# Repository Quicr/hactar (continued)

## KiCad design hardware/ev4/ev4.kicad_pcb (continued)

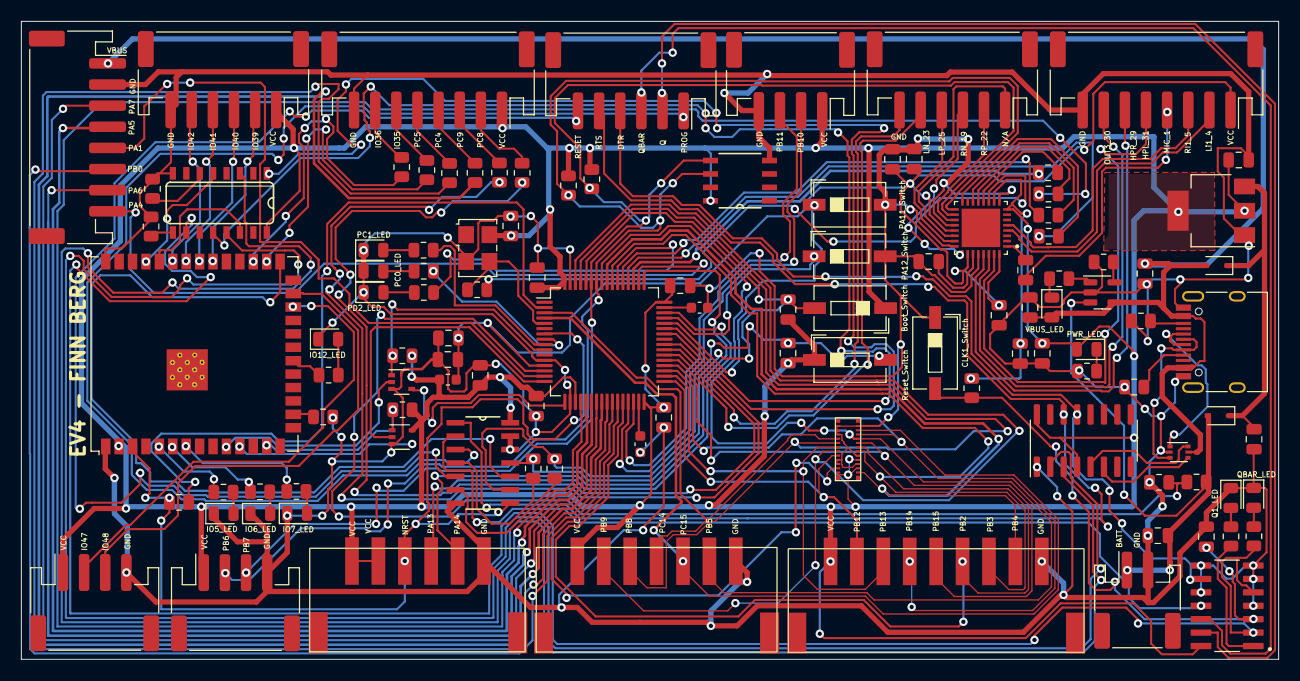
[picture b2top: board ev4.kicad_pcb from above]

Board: 2 copper layers, 119.0 x 60.4 mm, 111 parts (0 on the bottom side), 136 nets.

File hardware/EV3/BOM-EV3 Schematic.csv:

Comment,Designator,Footprint,LCSC
6.8k,R39,R_0805_2012Metric,C102042
NC7SZ125P5X,"U3,U9",SOT-353_SC-70-5,C12519
FerriteBead,120R1,L_0805_2012Metric,C127301
LED,"D1,D11,D3,D4,D5,D6,D7,D8,D9",LED_0805_2012Metric,C130114
DIODE,"D10,D2",D_0805_2012Metric,C133103
STM32F405RGTx,U1,LQFP-64_10x10mm_P0.5mm,C15742
USB_C_Receptacle,J9,USB_C_Receptacle_HRO_TYPE-C-31-M-12,C165948
10n,C8,C_0805_2012Metric,C1710
150,R1,R_0805_2012Metric,C17471
220,"R26,R30,R33,R34,R35",R_0805_2012Metric,C17557
4k7,"R13,R2,R3,R32,R4",R_0805_2012Metric,C17673
WM8960CGEFL/RV,U14,QFN50P500X500X90-33N,C18752
SG-5032CAN,X1,Oscillator_SMD_SeikoEpson_SG8002LB-4Pin_5.0x3.2mm,C1987261
100,"R14,R27,R28,R29,R31",R_0805_2012Metric,C212282
Conn_01x04_Female,"J3,J5,J7,J8",JST_PH_S4B-PH-SM4-TB_1x04-1MP_P2.00mm_Horizontal,C265102
Conn_01x08_Female,"J4,J6",JST_PH_S8B-PH-SM4-TB_1x08-1MP_P2.00mm_Horizontal,C265121
Conn_01x06_Female,J2,JST_PH_S6B-PH-SM4-TB_1x06-1MP_P2.00mm_Horizontal,C265405
SW_Push,"SW1,SW10,SW2,SW3,SW4,SW9",SW_DIP_SPSTx01_Slide_6.7x4.1mm_W6.73mm_P2.54mm_LowProfile_JPin,C266189
5k1,"R11,R12",R_0805_2012Metric,C27834
USBLC6-2P6,U4,SOT-666,C2827693
1u,"C10,C9",C_0805_2012Metric,C28323
1x6_connector,"U18,U5,U8",1x6_connector,C2845687
1x7_connector,U6,1x7_connector,C2845688
1x9_connector,U7,1x9_connector,C2845690
2k,R37,R_0805_2012Metric,C285226
560,"R10,R17,R18,R19,R20,R23,R24,R25,R9",R_0805_2012Metric,C28636
ESP32-S3-WROOM-1-N8R2,U11,ESP32-S3-WROOM-1-N8R2,C2913204
Conn_01x02_Female,J1,JST_PH_S2B-PH-SM4-TB_1x02-1MP_P2.00mm_Horizontal,C295747
AMS1117-3.3,U2,SOT-223-3_TabPin2,C351784
1k,R36,R_0805_2012Metric,C408924
4u7,"C1,C15,C19,C7",C_0805_2012Metric,C412634
MCP73832-2-OT,U12,SOT-23-5,C424093
BM20B(0.8)-24DS-0.4V(51),U16,BM20B(0.8)-24DS-0.4V(51),C424537
1k5,"R7,R8",R_0805_2012Metric,C4310
22u,C2,C_0805_2012Metric,C45783
10k,"R15,R16,R38",R_0805_2012Metric,C465472
100n,"C11,C12,C13,C14,C16,C17,C18,C20,C3,C4,C5,C6",C_0805_2012Metric,C49678
M24C02-RDW6TP,CR1,M24C02-RDW6TP,C83836
CH340C,U10,SOIC-16_3.9x9.9mm_P1.27mm,C84681

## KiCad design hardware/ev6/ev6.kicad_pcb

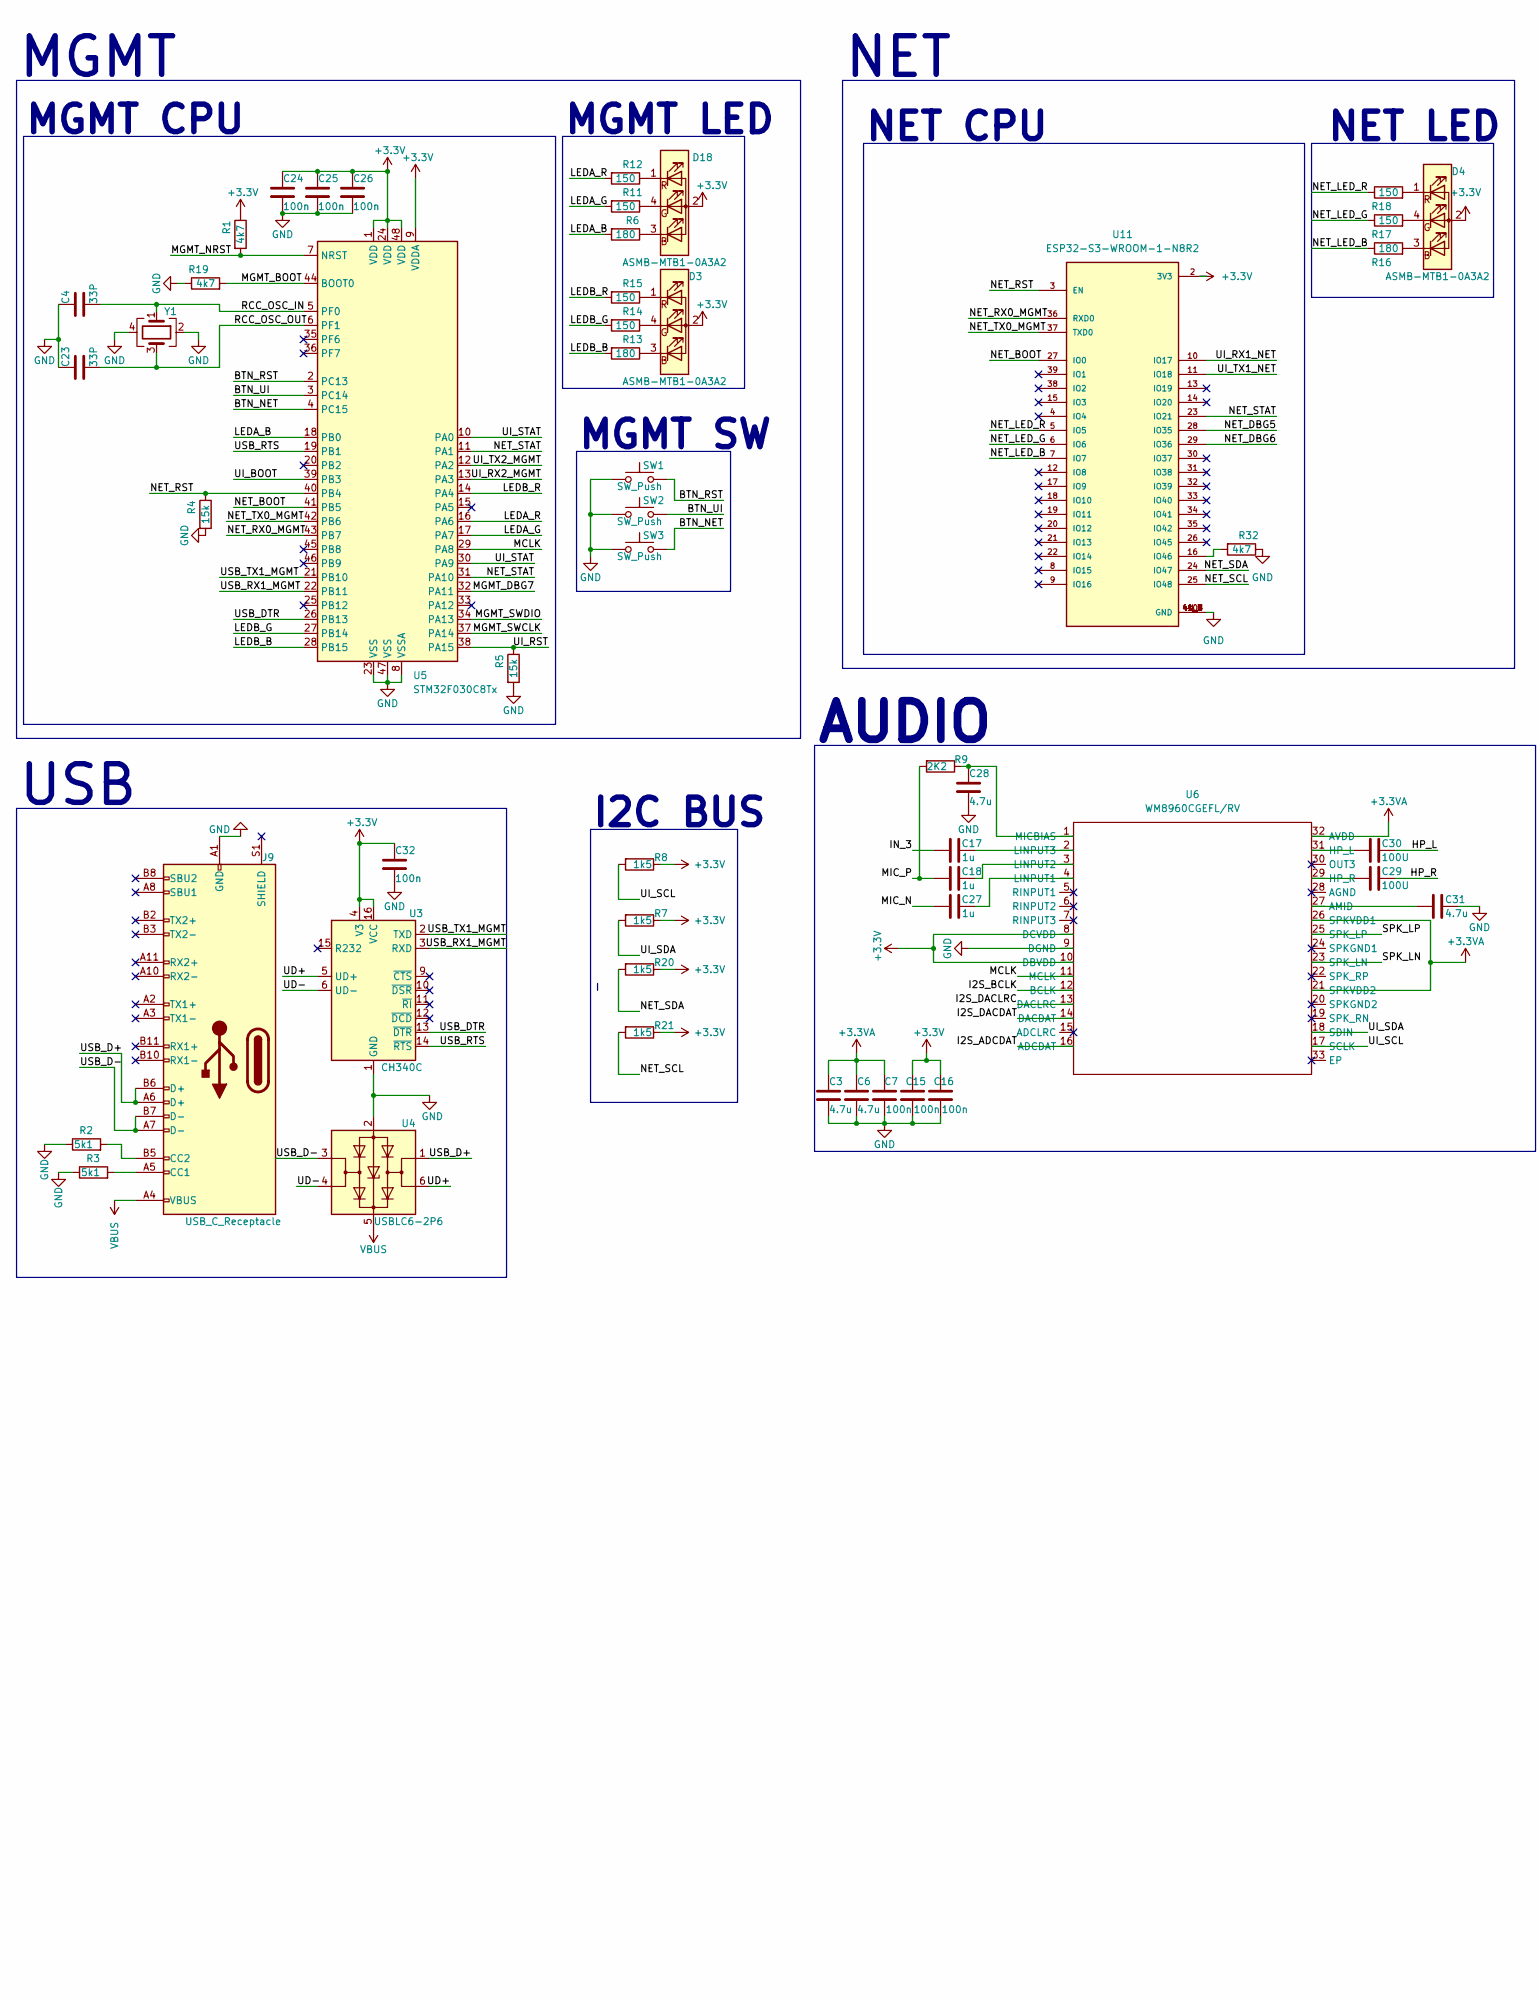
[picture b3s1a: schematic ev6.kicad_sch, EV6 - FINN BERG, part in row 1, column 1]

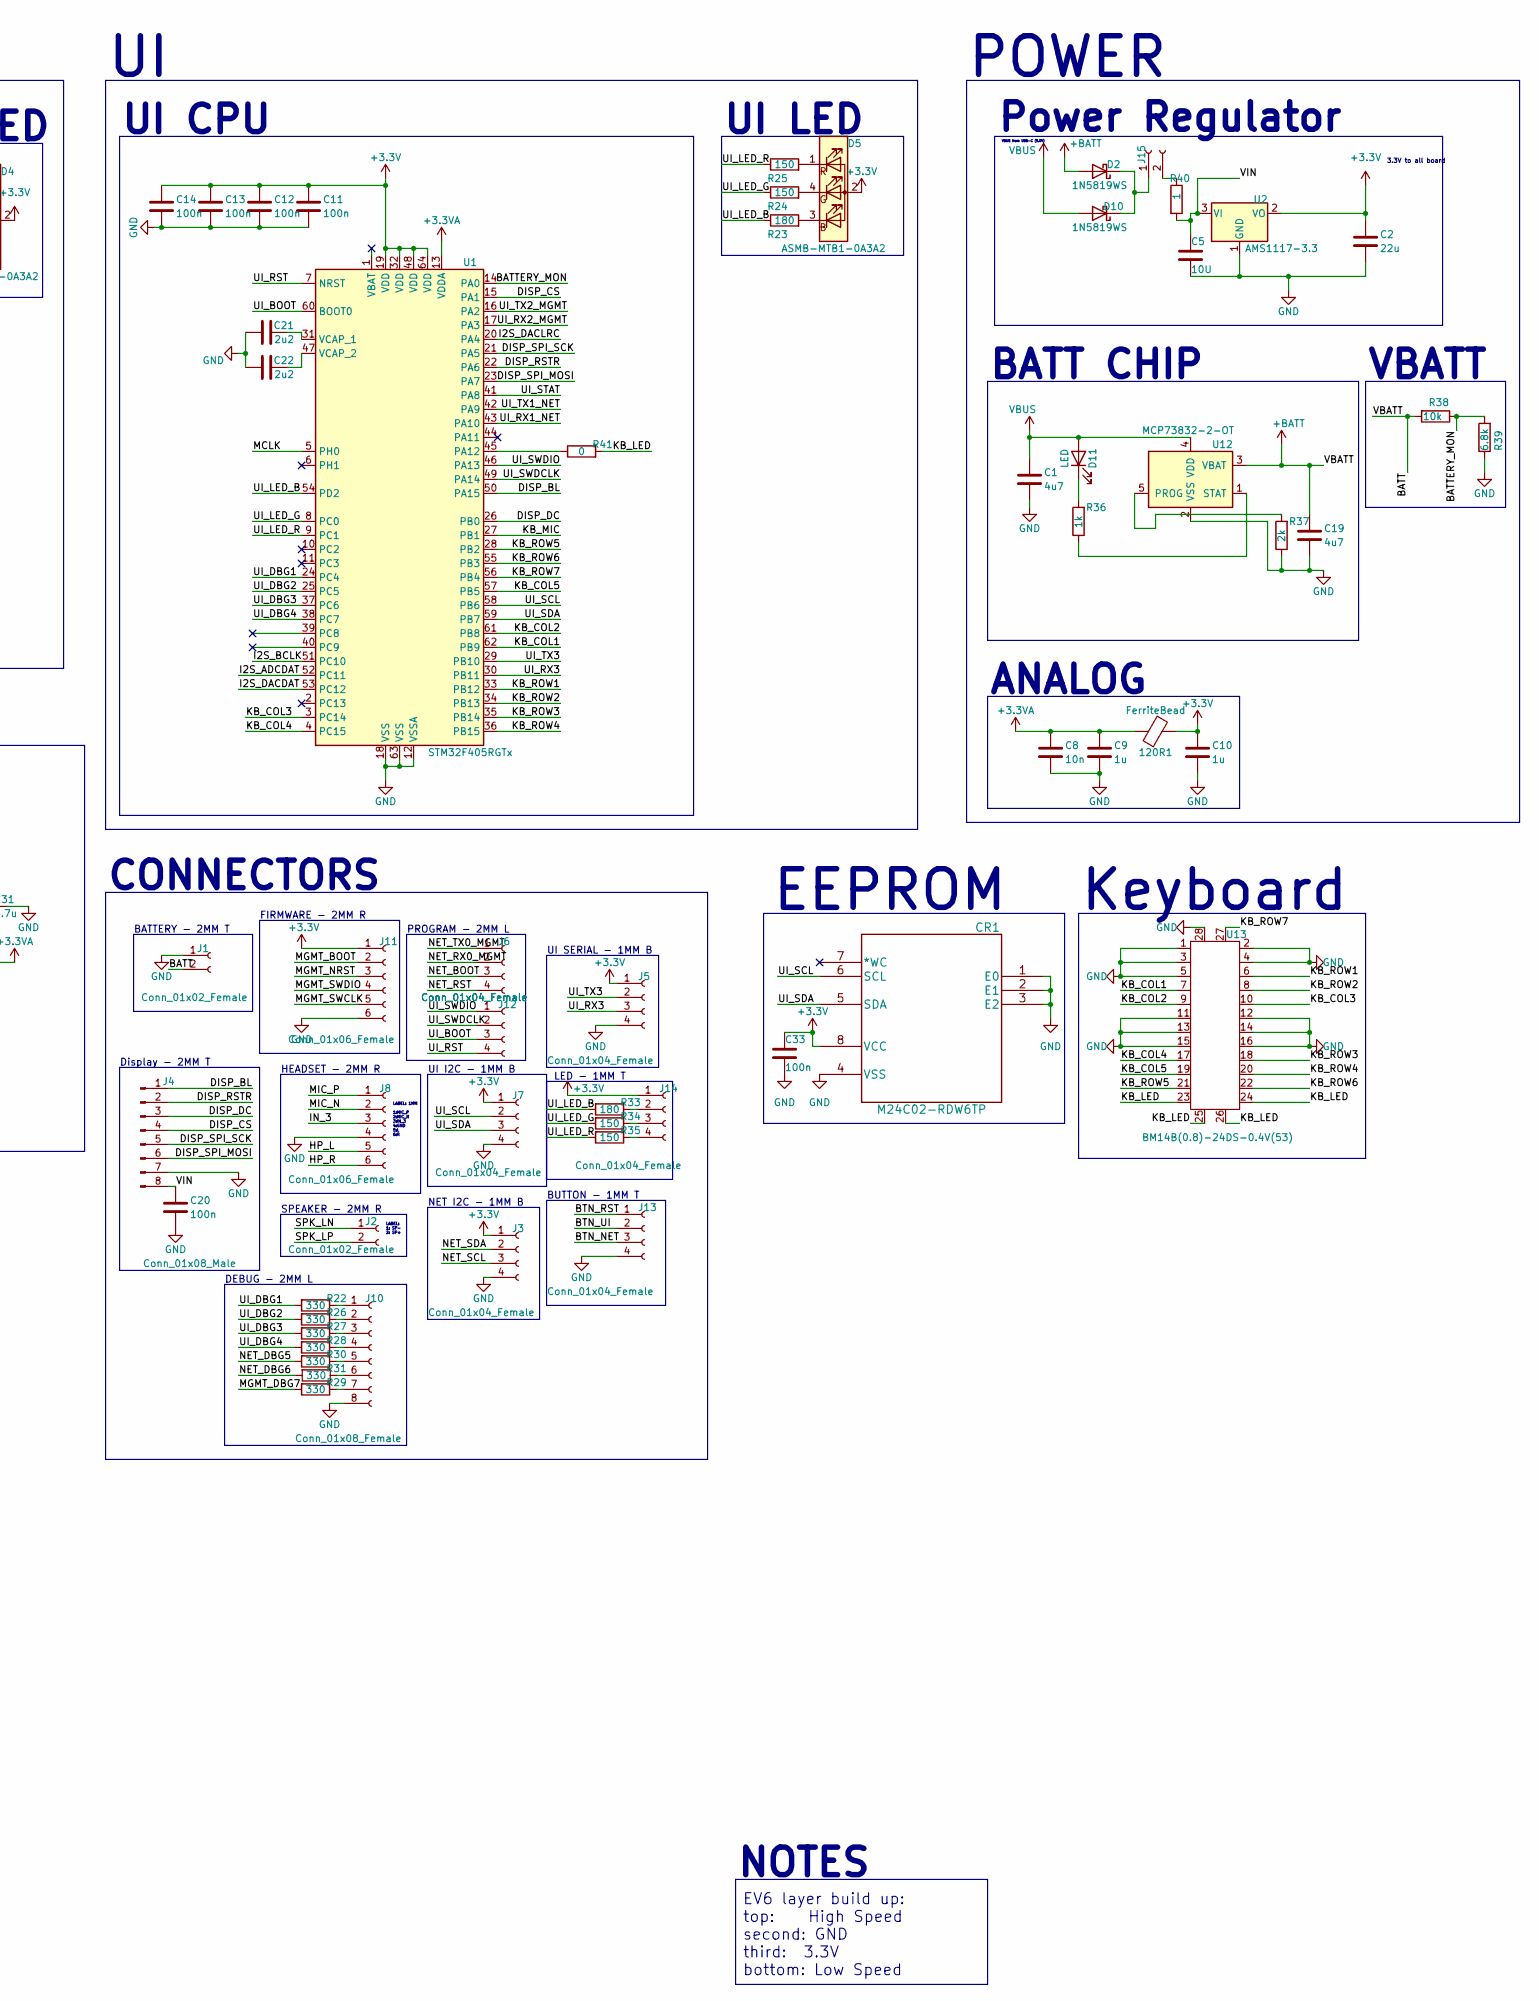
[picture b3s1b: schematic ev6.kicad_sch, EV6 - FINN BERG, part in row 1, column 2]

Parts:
120R1: FerriteBead; L_0603_1608Metric
C1, C19: 4u7; C_0402_1005Metric
C2: 22u; C_0402_1005Metric
C3, C6, C28, C31: 4.7u; C_0402_1005Metric
C4, C23: 33P; C_0805_2012Metric
C5: 10U; C_0402_1005Metric
C7, C11, C12, C13, C14, C15, C16, C20, C24, C25, C26, C32, C33: 100n; C_0402_1005Metric
C8: 10n; C_0402_1005Metric
C9, C10, C17, C18, C27: 1u; C_0402_1005Metric
C21, C22: 2u2; C_0402_1005Metric
C29, C30: 100U; C_1206_3216Metric
CR1: M24C02-RDW6TP; New_ESP32_M24C02-RMN6TP
D2, D10: 1N5819WS; D_SOD-323
D3, D4, D5, D18: ASMB-MTB1-0A3A2; LED RGB
D11: LED; LED_0805_2012Metric
J1, J2, J15: Conn_01x02_Female; JST_PH_S2B-PH-SM4-TB_1x02-1MP_P2.00mm_Horizontal
J3, J5, J6, J7, J12, J13, J14: Conn_01x04_Female; 1x4pin 1mm connector
J4: Conn_01x08_Male; PinHeader_1x08_P2.54mm_Vertical
J8, J11: Conn_01x06_Female; JST_PH_S6B-PH-SM4-TB_1x06-1MP_P2.00mm_Horizontal
J9: USB_C_Receptacle; USB_C_Receptacle_HRO_TYPE-C-31-M-12
J10: Conn_01x08_Female; JST_PH_S8B-PH-SM4-TB_1x08-1MP_P2.00mm_Horizontal
R1, R19, R32: 4k7; R_0402_1005Metric
R2, R3: 5k1; R_0402_1005Metric
R4, R5: 15k; R_0402_1005Metric
R6, R13, R16, R23, R33: 180; R_0402_1005Metric
R7, R8, R20, R21: 1k5; R_0402_1005Metric
R9: 2K2; R_0402_1005Metric
R11, R12, R14, R15, R17, R18, R24, R25, R34, R35: 150; R_0402_1005Metric
R22, R26, R27, R28, R29, R30, R31: 330; R_0402_1005Metric
R36: 1k; R_0402_1005Metric
R37: 2k; R_0402_1005Metric
R38: 10k; R_0402_1005Metric
R39: 6.8k; R_0402_1005Metric
R40: 1; R_0402_1005Metric
R41: 0; R_0402_1005Metric
SW1, SW2, SW3: SW_Push; SW_DIP_SPSTx01_Slide_6.7x4.1mm_W6.73mm_P2.54mm_LowProfile_J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
U1: STM32F405RGTx; LQFP-64_10x10mm_P0.5mm
U2: AMS1117-3.3; SOT-223-3_TabPin2
U3: CH340C; SOIC-16_3.9x9.9mm_P1.27mm
U4: USBLC6-2P6; SOT-666
U5: STM32F030C8Tx; LQFP-48_7x7mm_P0.5mm
U6: WM8960CGEFL/RV; QFN50P500X500X90-33N
U11: ESP32-S3-WROOM-1-N8R2; ESP32-S3-WROOM-1U
U12: MCP73832-2-OT; SOT-23-5
U13: BM14B(0.8)-24DS-0.4V(53); BM14B(0.B)-24DS-0.4V(53)
Y1: Crystal_GND24; Crystal_SMD_3225-4Pin_3.2x2.5mm

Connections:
+3.3V: 120R1.2, C2.1, C10.1, C11.1, C12.1, C13.1, C14.1, C15.2, C16.2, C24.1, C25.1, C26.1, C32.1, C33.1, CR1.8 (VCC), D3.2 (A), D4.2 (A), D5.2 (A), D18.2 (A), J3.1, J5.1, J7.1, J11.1, J14.1, R1.1, R7.1, R8.1, R20.1, R21.1, U1.19 (VDD), U1.32 (VDD), U1.48 (VDD), U1.64 (VDD), U2.2 (VO), U3.4 (V3), U3.16 (VCC), U5.1 (VDD), U5.9 (VDDA), U5.24 (VDD), U5.48 (VDD), U6.8 (DCVDD), U6.10 (DBVDD), U11.2 (3V3)
+3.3VA: 120R1.1, C3.1, C6.1, C7.2, C8.1, C9.1, U1.13 (VDDA), U6.21 (SPKVDD2), U6.26 (SPKVDD1), U6.32 (AVDD)
+BATT: C19.1, D2.2 (A), J1.2, R38.2, U12.3 (VBAT)
/BATTERY_MON: R38.1, R39.2, U1.14 (PA0)
/BTN_NET: J13.3, SW3.1, U5.4 (PC15)
/BTN_RST: J13.1, SW1.1, U5.2 (PC13)
/BTN_UI: J13.2, SW2.1, U5.3 (PC14)
/DISP_BL: J4.1, U1.50 (PA15)
/DISP_CS: J4.4, U1.15 (PA1)
/DISP_DC: J4.3, U1.26 (PB0)
/DISP_RSTR: J4.2, U1.22 (PA6)
/DISP_SPI_MOSI: J4.6, U1.23 (PA7)
/DISP_SPI_SCK: J4.5, U1.21 (PA5)
/HP_L: C30.2, J8.5
/HP_R: C29.2, J8.6
/I2S_ADCDAT: U1.52 (PC11), U6.16 (ADCDAT)
/I2S_BCLK: U1.51 (PC10), U6.12 (BCLK)
/I2S_DACDAT: U1.53 (PC12), U6.14 (DACDAT)
/I2S_DACLRC: U1.20 (PA4), U6.13 (DACLRC)
/IN_3: C17.1, J8.3
/KB_COL1: U1.62 (PB9), U13.7
/KB_COL2: U1.61 (PB8), U13.9
/KB_COL3: U1.3 (PC14), U13.10
/KB_COL4: U1.4 (PC15), U13.17
/KB_COL5: U1.57 (PB5), U13.19
/KB_LED: R41.2, U13.23, U13.24, U13.25, U13.26
/KB_MIC: U1.27 (PB1)
/KB_ROW1: U1.33 (PB12), U13.6
/KB_ROW2: U1.34 (PB13), U13.8
/KB_ROW3: U1.35 (PB14), U13.18
/KB_ROW4: U1.36 (PB15), U13.20
/KB_ROW5: U1.28 (PB2), U13.21
/KB_ROW6: U1.55 (PB3), U13.22
/KB_ROW7: U1.56 (PB4), U13.27
/LEDA_B: R6.2, U5.18 (PB0)
/LEDA_G: R11.2, U5.17 (PA7)
/LEDA_R: R12.2, U5.16 (PA6)
/LEDB_B: R13.2, U5.28 (PB15)
/LEDB_G: R14.2, U5.27 (PB14)
/LEDB_R: R15.2, U5.14 (PA4)
/MCLK: U1.5 (PH0), U5.29 (PA8), U6.11 (MCLK)
/MGMT_BOOT: J11.2, R19.2, U5.44 (BOOT0)
/MGMT_DBG7: R29.2, U5.32 (PA11)
/MGMT_NRST: J11.3, R1.2, U5.7 (NRST)
/MGMT_SWCLK: J11.5, U5.37 (PA14)
/MGMT_SWDIO: J11.4, U5.34 (PA13)
/MIC_N: C27.1, J8.2
/MIC_P: C18.1, J8.1, R9.2
/NET_BOOT: J6.3, U5.41 (PB5), U11.27 (IO0)
/NET_DBG5: R30.2, U11.28 (IO35)
/NET_DBG6: R31.2, U11.29 (IO36)
/NET_LED_B: R16.1, U11.7 (IO7)
/NET_LED_G: R17.1, U11.6 (IO6)
/NET_LED_R: R18.1, U11.5 (IO5)
/NET_RST: J6.4, R4.1, U5.40 (PB4), U11.3 (EN)
/NET_RX0_MGMT: J6.2, U5.43 (PB7), U11.36 (RXD0)
/NET_SCL: J3.3, R21.2, U11.25 (IO48)
/NET_SDA: J3.2, R20.2, U11.24 (IO47)
/NET_STAT: U5.11 (PA1), U5.31 (PA10), U11.23 (IO21)
/NET_TX0_MGMT: J6.1, U5.42 (PB6), U11.37 (TXD0)
/RCC_OSC_IN: C4.2, U5.5 (PF0), Y1.1
/RCC_OSC_OUT: C23.2, U5.6 (PF1), Y1.3
/SPK_LN: J2.1, U6.23 (SPK_LN)
/SPK_LP: J2.2, U6.25 (SPK_LP)
/UD+: U3.5 (UD+), U4.6 (I/O1)
/UD-: U3.6 (UD-), U4.4 (I/O2)
/UI_BOOT: J12.3, U1.60 (BOOT0), U5.39 (PB3)
/UI_DBG1: R22.2, U1.24 (PC4)
/UI_DBG2: R26.2, U1.25 (PC5)
/UI_DBG3: R27.2, U1.37 (PC6)
/UI_DBG4: R28.2, U1.38 (PC7)
/UI_LED_B: R23.1, R33.2, U1.54 (PD2)
/UI_LED_G: R24.1, R34.2, U1.8 (PC0)
/UI_LED_R: R25.1, R35.2, U1.9 (PC1)
/UI_RST: J12.4, R5.1, U1.7 (NRST), U5.38 (PA15)
/UI_RX1_NET: U1.43 (PA10), U11.10 (IO17)
/UI_RX2_MGMT: U1.17 (PA3), U5.13 (PA3)
/UI_RX3: J5.3, U1.30 (PB11)
/UI_SCL: CR1.6 (SCL), J7.2, R8.2, U1.58 (PB6), U6.17 (SCLK)
/UI_SDA: CR1.5 (SDA), J7.3, R7.2, U1.59 (PB7), U6.18 (SDIN)
/UI_STAT: U1.41 (PA8), U5.10 (PA0), U5.30 (PA9)
/UI_SWDCLK: J12.2, U1.49 (PA14)
/UI_SWDIO: J12.1, U1.46 (PA13)
/UI_TX1_NET: U1.42 (PA9), U11.11 (IO18)
/UI_TX2_MGMT: U1.16 (PA2), U5.12 (PA2)
/UI_TX3: J5.2, U1.29 (PB10)
/USB_D+: J9.A6 (D+), J9.B6 (D+), U4.1 (I/O1)
/USB_D-: J9.A7 (D-), J9.B7 (D-), U4.3 (I/O2)
/USB_DTR: U3.13 (~DTR), U5.26 (PB13)
/USB_RTS: U3.14 (~RTS), U5.19 (PB1)
/USB_RX1_MGMT: U3.3 (RXD), U5.22 (PB11)
/USB_TX1_MGMT: U3.2 (TXD), U5.21 (PB10)
/VIN: C5.1, C20.1, J4.8, R40.2, U2.3 (VI)
GND: C1.2, C2.2, C3.2, C4.1, C5.2, C6.2, C7.1, C8.2, C9.2, C10.2, C11.2, C12.2, C13.2, C14.2, C15.1, C16.1, C19.2, C20.2, C21.1, C22.1, C23.1, C24.2, C25.2, C26.2, C28.2, C31.1, C32.2, C33.2, CR1.1 (E0), CR1.2 (E1), CR1.3 (E2), CR1.4 (VSS), J1.1, J3.4, J4.7, J5.4, J7.4, J8.4, J9.A1 (GND), J9.A12 (GND), J9.B1 (GND), J9.B12 (GND), J10.8, J11.6, J13.4, R2.1, R3.1, R4.2, R5.2, R19.1, R32.1, R37.1, R39.1, SW1.2, SW2.2, SW3.2, U1.12 (VSSA), U1.18 (VSS), U1.63 (VSS), U2.1 (GND), U3.1 (GND), U4.2 (GND), U5.8 (VSSA), U5.23 (VSS), U5.47 (VSS), U6.9 (DGND), U11.1 (GND), U11.40 (GND), U11.41_1 (GND), U11.41_2 (GND), U11.41_3 (GND), U11.41_4 (GND), U11.41_5 (GND), U11.41_6 (GND), U11.41_7 (GND), U11.41_8 (GND), U11.41_9 (GND), U12.2 (VSS), U13.1, U13.2, U13.3, U13.4, U13.5, U13.11, U13.12, U13.13, U13.14, U13.15, U13.16, U13.28, Y1.2, Y1.4
unnamed: C17.2, U6.2 (LINPUT3)
unnamed: C18.2, U6.3 (LINPUT2)
unnamed: C21.2, U1.31 (VCAP_1)
unnamed: C22.2, U1.47 (VCAP_2)
unnamed: C27.2, U6.4 (LINPUT1)
unnamed: C28.1, R9.1, U6.1 (MICBIAS)
unnamed: C29.1, U6.29 (HP_R)
unnamed: C30.1, U6.31 (HP_L)
unnamed: C31.2, U6.27 (AMID)
unnamed: D3.1 (RK), R15.1
unnamed: D3.3 (BK), R13.1
unnamed: D3.4 (GK), R14.1
unnamed: D4.1 (RK), R18.2
unnamed: D4.3 (BK), R16.2
unnamed: D4.4 (GK), R17.2
unnamed: D5.1 (RK), R25.2
unnamed: D5.3 (BK), R23.2
unnamed: D5.4 (GK), R24.2
unnamed: D2.1 (K), D10.1 (K), J15.1
unnamed: D11.1 (K), R36.2
unnamed: D18.1 (RK), R12.1
unnamed: D18.3 (BK), R6.1
unnamed: D18.4 (GK), R11.1
unnamed: J9.A5 (CC1), R3.2
unnamed: J9.B5 (CC2), R2.2
unnamed: J10.1, R22.1
unnamed: J10.2, R26.1
unnamed: J10.3, R27.1
unnamed: J10.4, R28.1
unnamed: J10.5, R30.1
unnamed: J10.6, R31.1
unnamed: J10.7, R29.1
unnamed: J14.2, R33.1
unnamed: J14.3, R34.1
unnamed: J14.4, R35.1
unnamed: J15.2, R40.1
unnamed: R32.2, U11.16 (IO46)
unnamed: R36.1, U12.1 (STAT)
unnamed: R37.2, U12.5 (PROG)
unnamed: R41.1, U1.45 (PA12)
VBUS: C1.1, D10.2 (A), D11.2 (A), J9.A4 (VBUS), J9.A9 (VBUS), J9.B4 (VBUS), J9.B9 (VBUS), U4.5 (VBUS), U12.4 (VDD)

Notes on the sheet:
MGMT
VBATT
SPEAKER - 2MM R
NET CPU
MGMT CPU
BATT CHIP
NET
POWER
PROGRAM - 2MM L
CONNECTORS
3.3V to all board
NET LED
UI CPU
HEADSET - 2MM R
BATTERY - 2MM T
BUTTON - 1MM T
EV6 layer build up: top: High Speed second: GND third: 3.3V bottom: Low Speed
LABEL: 1MM 1:MIC_P 2:MIC_N 3:IN_3 4:GND 5:L 6:R
AUDIO
MGMT SW
UI SERIAL - 1MM B
EEPROM
UI I2C - 1MM B
I2C BUS
FIRMWARE - 2MM R
USB
VBUS from USB-C (5.0V)
MGMT LED
LABEL: 1: SP- 2: SP+
LED - 1MM T
NOTES
Power Regulator
Keyboard
Display - 2MM T
DEBUG - 2MM L
UI LED
NET I2C - 1MM B
ANALOG

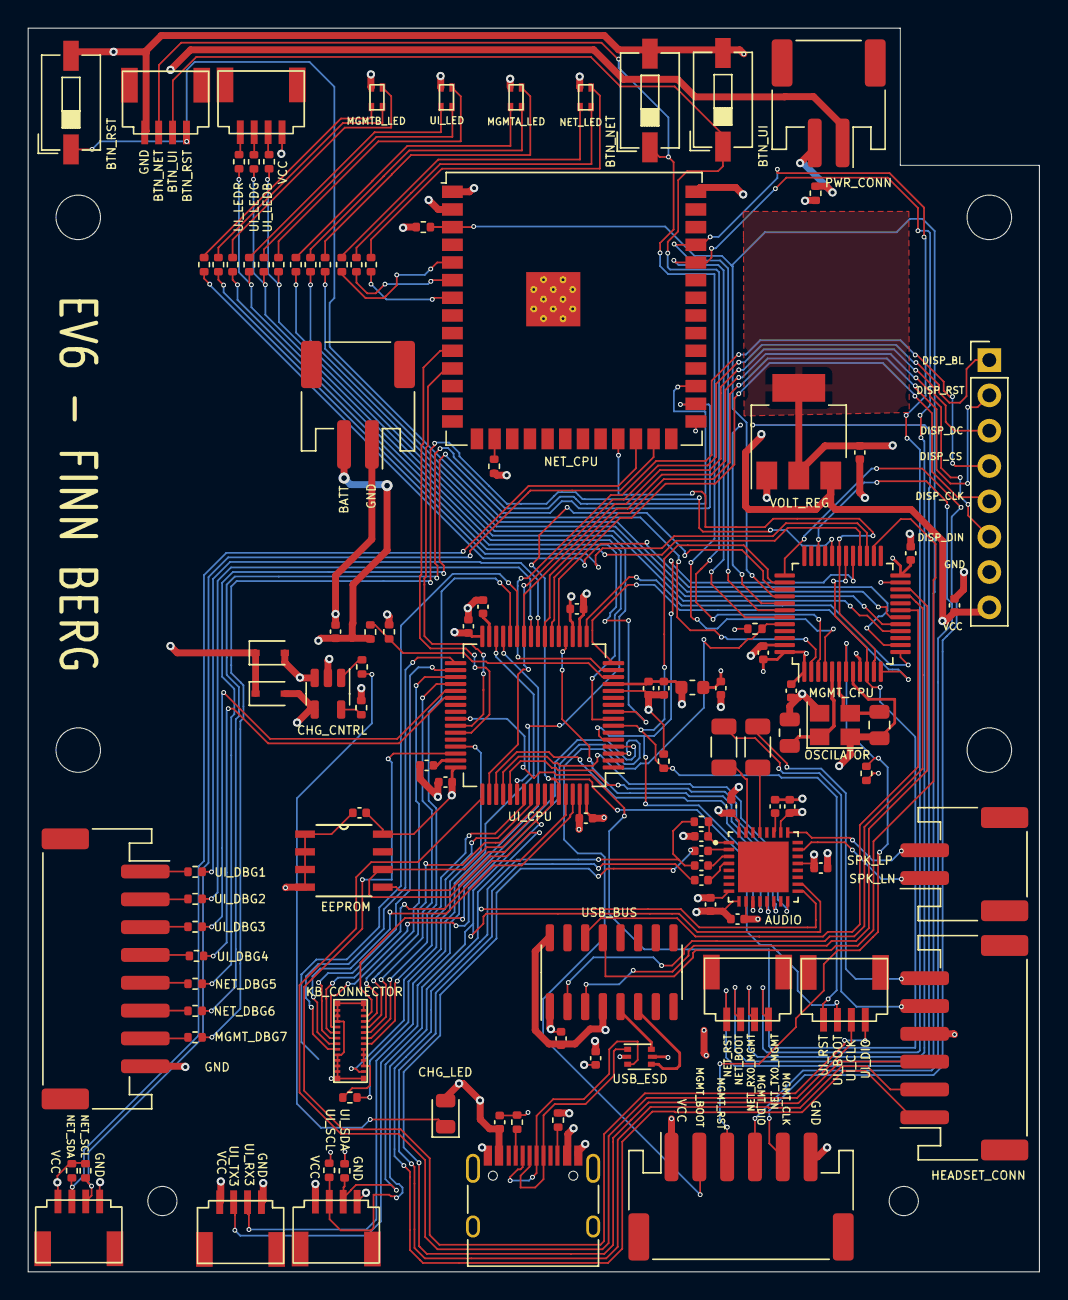
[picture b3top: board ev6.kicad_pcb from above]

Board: 4 copper layers, 72.7 x 89.4 mm, 110 parts (0 on the bottom side), 134 nets.
